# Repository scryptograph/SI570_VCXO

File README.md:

# SI570_VCXO
Silicon Labs SI570 Powered Voltage Controlled Crystal Oscillator with I2C interfacing with MSP430G2553 IC

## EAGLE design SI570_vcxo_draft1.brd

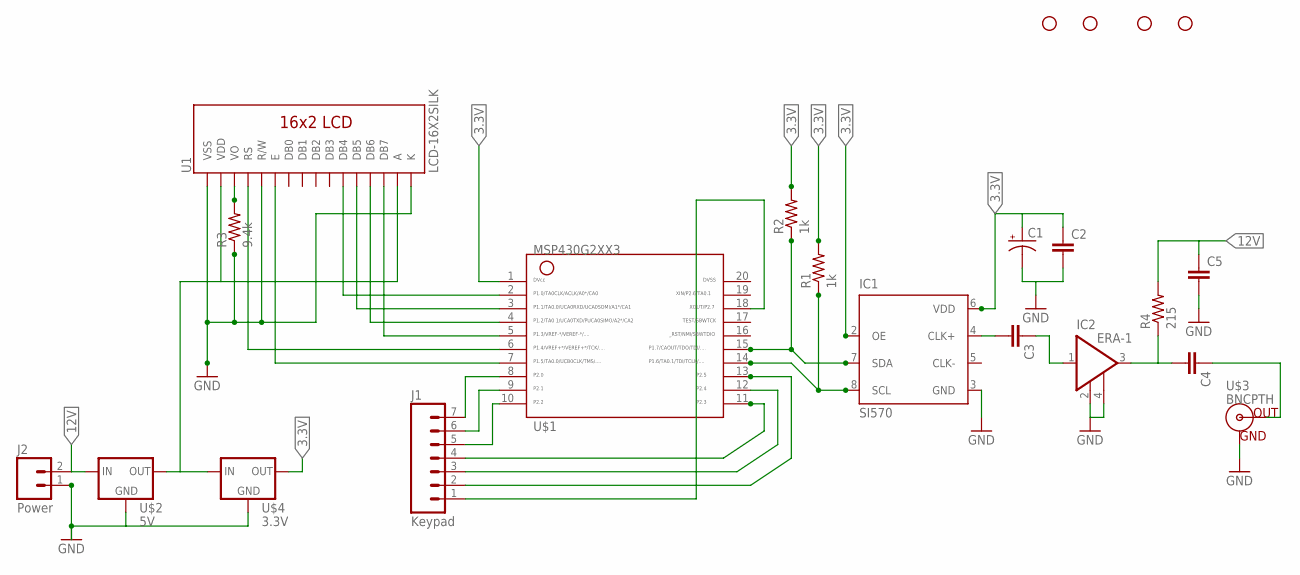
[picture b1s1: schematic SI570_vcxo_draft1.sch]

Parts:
C1: 100UF-25V-20%(PTH); CPOL-RADIAL-100UF-25V
C2, C3, C4, C5: CAP0603-CAP; 0603-CAP
H1, H2, H3, H4: STAND-OFF
IC1: SI570; 8-PIN
IC2: ERA-1; VV
J1: Keypad; 1X07
J2: Power; 1X02
R1, R2: 1k; AXIAL-0.3EZ
R3: 9.4k; AXIAL-0.3EZ
R4: 215; AXIAL-0.3EZ
U1: LCD-16X2SILK; LCD-16X2
U$1: G2XX3---N20; N20
U$2: 5V; LD1117V33
U$3: BNCPTH; BNC
U$4: 3.3V; LD1117V33

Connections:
3.3V: C1.1 (+), C2.1, IC1.2 (OE), IC1.6 (VDD), R1.P$2 (2), R2.P$2 (2), U$1.1, U$4.OUT
12V: C5.1, J2.2, R4.P$2 (2), U$2.IN
GND: C1.2 (-), C2.2, C5.2, IC1.3 (GND), IC2.2 (GND), IC2.4 (GND), J2.1, R3.P$1 (1), U1.1 (VSS), U1.5 (R/W), U1.16 (K), U$2.GND, U$3.GND, U$4.GND
unnamed: IC1.7 (SDA), R2.P$1 (1), U$1.15
unnamed: IC1.8 (SCL), R1.P$1 (1), U$1.14
unnamed: R3.P$2 (2), U1.3 (VO)
unnamed: C4.2, IC2.3 (RFOUT/DCIN), R4.P$1 (1)
unnamed: U1.4 (RS), U$1.6
unnamed: C3.2, IC1.4 (CLK+)
unnamed: U1.6 (E), U$1.7
unnamed: U1.11 (DB4), U$1.2
unnamed: U1.12 (DB5), U$1.3
unnamed: U1.13 (DB6), U$1.4
unnamed: U1.14 (DB7), U$1.5
unnamed: J1.7, U$1.8
unnamed: J1.6, U$1.9
unnamed: J1.5, U$1.10
unnamed: C3.1, IC2.1 (RFIN)
unnamed: J1.4, U$1.11
unnamed: J1.3, U$1.12
unnamed: J1.2, U$1.13
unnamed: J1.1, U$1.18
unnamed: C4.1, U$3.S (OUT)
unnamed: U1.2 (VDD), U1.15 (A), U$2.OUT, U$4.IN

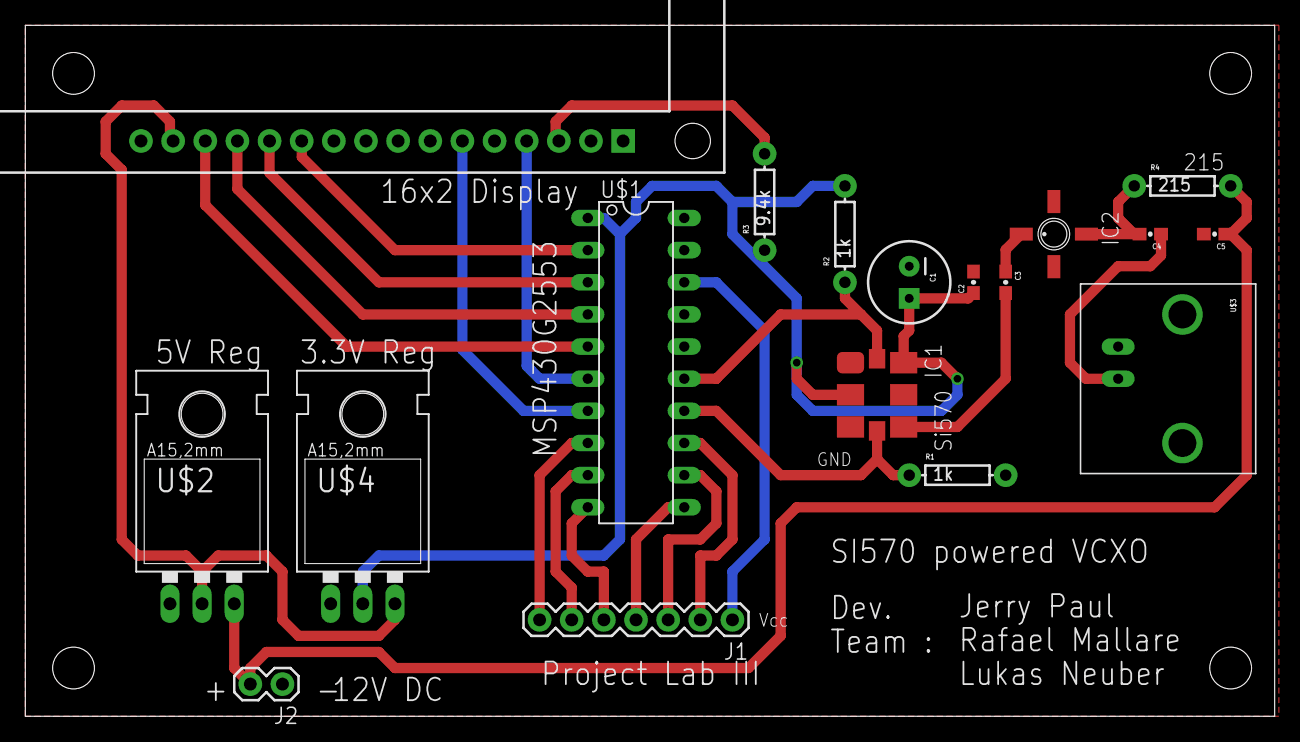
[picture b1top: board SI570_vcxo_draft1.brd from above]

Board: 2 copper layers, 98.7 x 54.6 mm, 22 parts (0 on the bottom side), 24 nets.

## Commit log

2016-04-18 Schematic/Board Files updated
2016-04-18 Images Added

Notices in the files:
parts and their libraries:
SparkFun-Capacitors: Licensing: Creative Commons ShareAlike 4.0 International - https://creativecommons.org/licenses/by-sa/4.0
